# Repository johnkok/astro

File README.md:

# Raspberry Pi astrophotography mount stack

This repository is the reproducible source of truth for the custom Servo42D
equatorial mount used with PINS/N.I.N.A., INDI, and PHD2 on Raspberry Pi.
It contains the Python ASCOM Alpaca driver, the timed-guide extension to INDI's
Alpaca telescope bridge, system services, sanitized application configuration,
and scripts for installing or validating a replacement Pi.

The reference system is a 64-bit Raspberry Pi running Debian 13 (trixie). Its
control path is:

```text
PINS/N.I.N.A. or PHD2
        |
        +-- INDI server :7624 -- indi_alpaca_telescope --+
        |                                                |
        +---------------- ASCOM Alpaca :11111 <----------+
                                     |
                              Servo42D driver
                                     |
                            SocketCAN can0 @ 500 kbit/s
                                     |
                         RA motor ID 2 / DEC motor ID 1
```

## Repository layout

- `drivers/servo42d-alpaca/` — complete Python Alpaca server source and tests.
- `drivers/indi-alpaca-telescope/` — the two modified INDI v2.2.5 source files.
- `rpi/` — systemd, SocketCAN, APT, INDI, and PINS configuration.
- `scripts/` — install, build, profile configuration, backup, and verification.
- `docs/` — architecture, deployment notes, source provenance, and Pi history.
- `3D/` — mechanical mount models already maintained in this repository.

Generated virtual environments, compiler output, logs, N.I.N.A. databases, and
full private profiles are intentionally excluded.

## New Pi quick start

Use a Raspberry Pi OS/Debian 13 arm64 image and create the `pi` user. Clone this
repository on the new Pi, review the hardware values in
`drivers/servo42d-alpaca/config.json` and `rpi/boot/config.txt.snippet`, then run:

```bash
cd astro
sudo ./scripts/install-rpi.sh
sudo reboot
./scripts/verify-rpi.sh
```

The installer adds the public Touch-N-Stars/PINS APT repository, installs PINS,
PHD2 and INDI, installs the Alpaca driver under `/opt`, builds the customized
INDI bridge from the pinned v2.2.5 source, configures CAN, restores the
non-private INDI/PINS files, and enables boot services.

After PINS/N.I.N.A. has created a profile, patch only its mount settings:

```bash
./scripts/configure-nina-profile.py \
  ~/.local/share/NINA/Profiles/YOUR-PROFILE.profile

./scripts/configure-phd2-profile.py ~/.PHDGuidingV2 --profile 2
```

The scripts create timestamped backups before changing profiles. Observatory
coordinates, camera serial numbers, credentials, sequences, and calibration
data remain local to each device.

## Development

Run the Alpaca driver without motors by changing `can.interface` to `virtual`
in a local config, then:

```bash
cd drivers/servo42d-alpaca
python3 -m venv .venv
. .venv/bin/activate
pip install -e '.[test]'
pytest
```

To rebuild only the customized INDI driver:

```bash
sudo ./scripts/build-indi-driver.sh
```

See `docs/REPRODUCE.md` before deploying to hardware. This prototype has no
limit-switch, collision-avoidance, homing, or meridian-flip safety layer.

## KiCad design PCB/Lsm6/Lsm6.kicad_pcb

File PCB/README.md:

# IM72D128V01XTMA1 MEMS microphone breakout

This KiCad project provides a small, simple breakout PCB for the IM72D128V01XTMA1 digital MEMS microphone.

## Included in the design

- Sensor footprint centered on the board
- 100 nF decoupling capacitor on VDD
- 10 kΩ pull-up to VDD on the SEL pin
- 5-pin header to expose VDD, GND, CLK, DATA, and SEL
- Compact 60 x 50 mm board outline for easy prototyping

## Notes

This is a practical reference board intended to be opened and adjusted in KiCad. The exact mechanical and pinout details should be confirmed against the manufacturer's latest datasheet before ordering bare boards or building a production design.

## Files

- `im72d128v01xtma1.kicad_pro` – KiCad project
- `im72d128v01xtma1.kicad_sch` – schematic
- `im72d128v01xtma1.kicad_pcb` – PCB layout

## Example signal map

- VDD: microphone supply rail
- GND: analog/digital ground
- CLK: digital clock output or input depending on interface
- DATA: digital audio data line
- SEL: mode select / left-right / configuration pin (verify against final datasheet)

The board is meant as a starting point for a digital MEMS audio interface, not as a final production release.

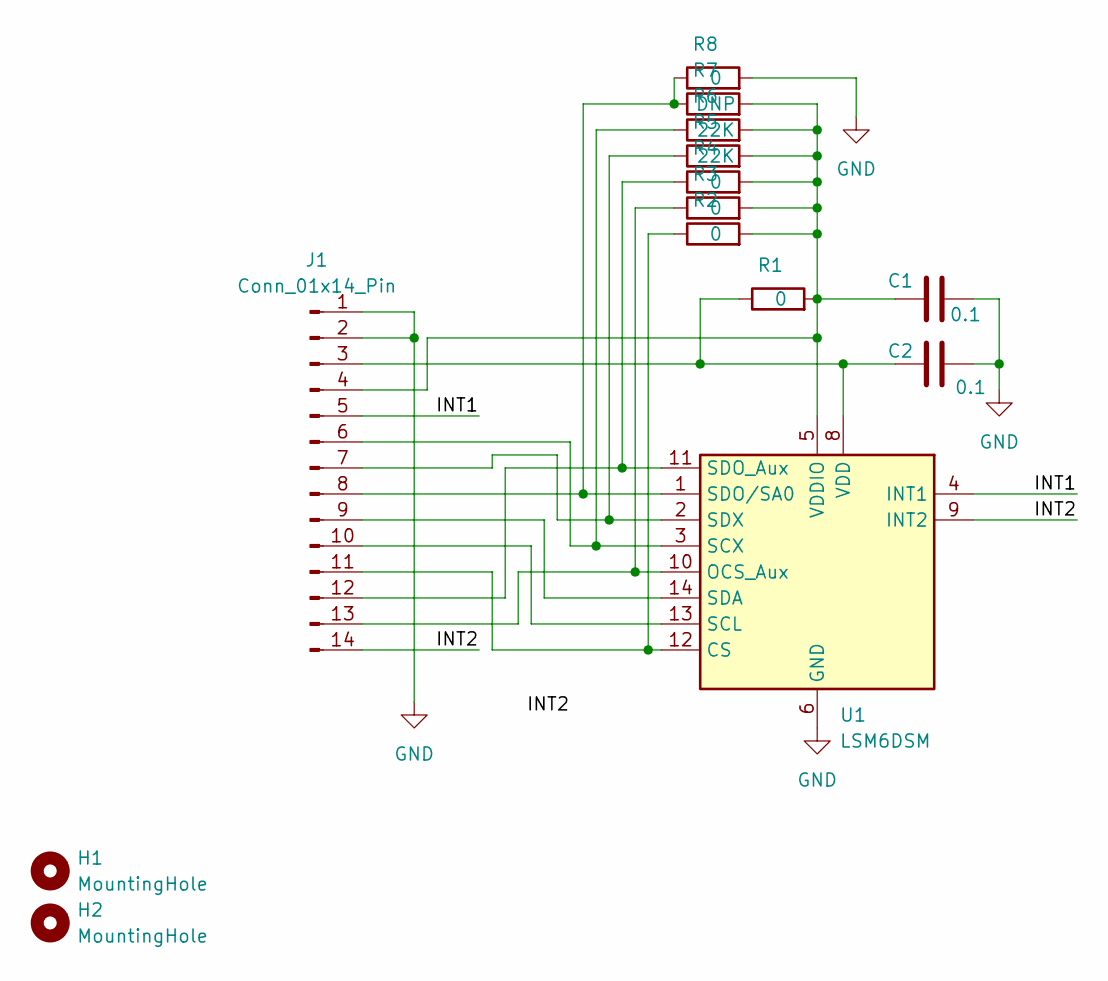
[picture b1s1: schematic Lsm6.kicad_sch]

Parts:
C1, C2: 0.1; C_0603_1608Metric_Pad1.08x0.95mm_HandSolder
H1, H2: MountingHole; MountingHole_3.2mm_M3_DIN965_Pad
J1: Conn_01x14_Pin; PinHeader_1x14_P1.27mm_Vertical
R1, R2, R3, R4, R8: 0; R_0603_1608Metric_Pad0.98x0.95mm_HandSolder
R5, R6: 22K; R_0603_1608Metric_Pad0.98x0.95mm_HandSolder
R7: DNP; R_0603_1608Metric_Pad0.98x0.95mm_HandSolder
U1: LSM6DSM; LGA-14_3x2.5mm_P0.5mm_LayoutBorder3x4y

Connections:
/INT1: J1.5, U1.4 (INT1)
/INT2: J1.14, U1.9 (INT2)
GND: C1.2, C2.2, J1.1, J1.2, R8.2, U1.6 (GND), U1.7 (GND)
unnamed: C2.1, J1.3, R1.1, U1.8 (VDD)
unnamed: C1.1, J1.4, R1.2, R2.2, R3.2, R4.2, R5.2, R6.2, R7.2, U1.5 (VDDIO)
unnamed: J1.6, R6.1, U1.3 (SCX)
unnamed: J1.7, R5.1, U1.2 (SDX)
unnamed: J1.8, R7.1, R8.1, U1.1 (SDO/SA0)
unnamed: J1.9, U1.14 (SDA)
unnamed: J1.10, U1.13 (SCL)
unnamed: J1.11, R2.1, U1.12 (CS)
unnamed: J1.12, R4.1, U1.11 (SDO_Aux)
unnamed: J1.13, R3.1, U1.10 (OCS_Aux)

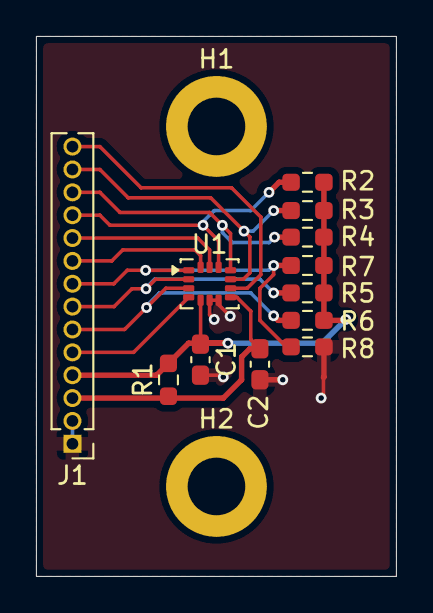
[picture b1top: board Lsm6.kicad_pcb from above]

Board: 2 copper layers, 20.0 x 30.0 mm, 14 parts (0 on the bottom side), 13 nets.
